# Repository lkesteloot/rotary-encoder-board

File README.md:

# Rotary encoder board for PEC11R.

This is a breakout board for the
[PEC11R](http://www.bourns.com/docs/Product-Datasheets/PEC11R.pdf) rotary
encoder. These encoders don't fit on breadboards. This board has pins that
sit nicely on breadboard spacing.

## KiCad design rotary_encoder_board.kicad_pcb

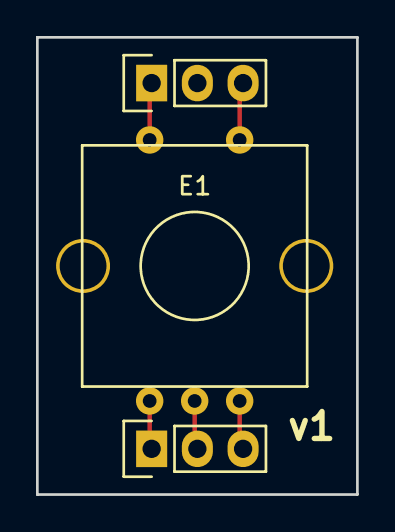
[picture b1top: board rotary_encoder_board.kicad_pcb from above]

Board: 2 copper layers, 17.8 x 25.4 mm, 3 parts (0 on the bottom side), 5 nets.

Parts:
E1: PEC11R; pec11r
P1, P2: CONN_01X03; Pin_Header_Straight_1x03

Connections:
unnamed: E1.1, P1.1
unnamed: E1.2, P1.3
unnamed: E1.A, P2.1
unnamed: E1.B, P2.3
unnamed: E1.C, P2.2

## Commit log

2016-01-19 Initial revision.
2016-01-19 Add README.
2016-01-19 Output gerber files.
